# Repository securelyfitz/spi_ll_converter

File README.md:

# spi_ll_converter
Sparkfun's logic level converter modified to add SPI headers

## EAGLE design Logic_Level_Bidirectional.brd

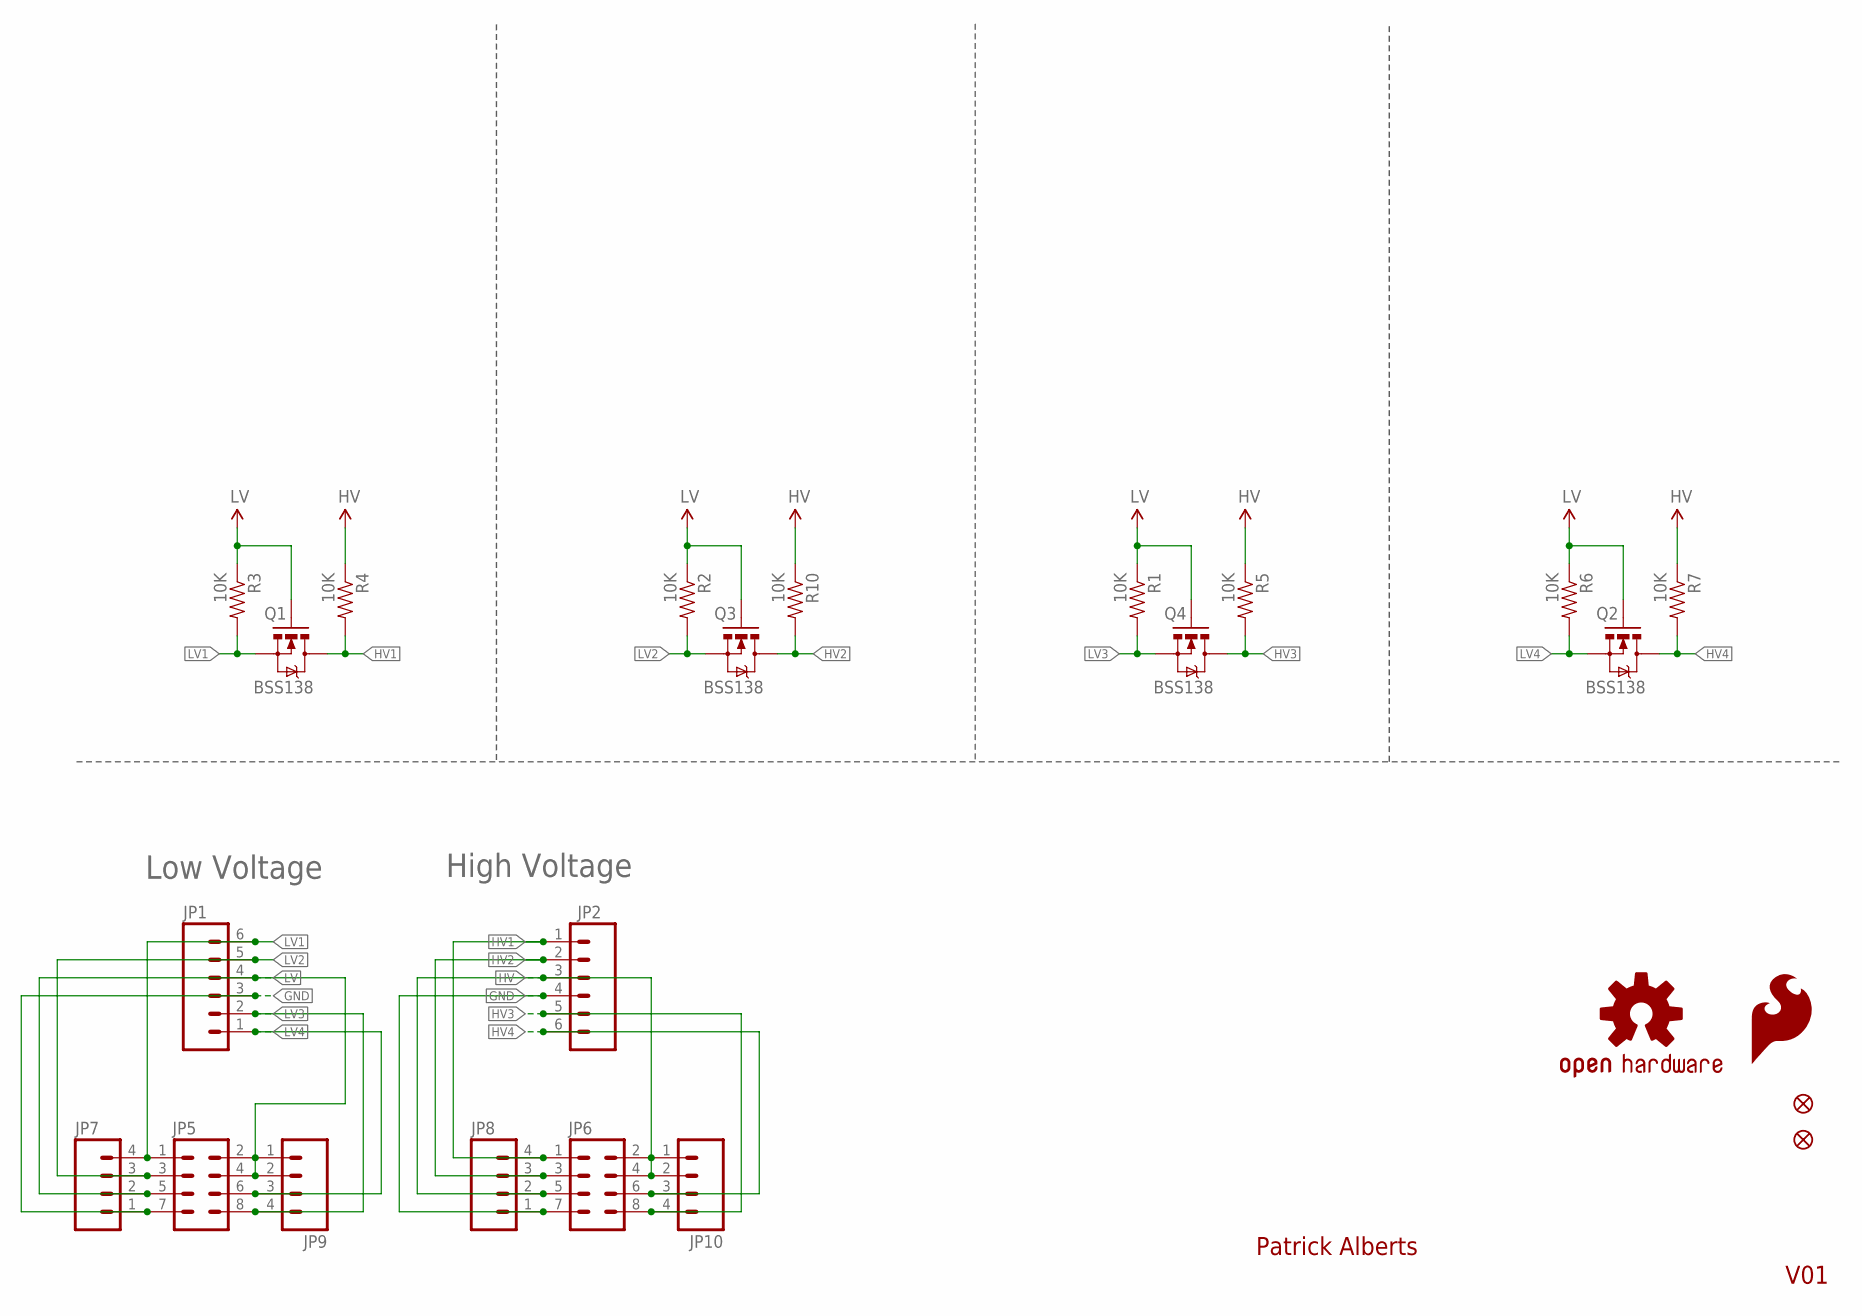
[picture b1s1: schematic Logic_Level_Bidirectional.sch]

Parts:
JP1, JP2: M06SIP; 1X06
JP3, JP4: FIDUCIALUFIDUCIAL; MICRO-FIDUCIAL
JP5, JP6: M04X2; 2X4
JP7, JP8: M04LOCK; 1X04_LOCK
JP9, JP10: M04PTH; 1X04
LOGO1: SFE_LOGO_FLAME.1_INCH; SFE_LOGO_FLAME_.1
LOGO2: OSHW-LOGOS; OSHW-LOGO-S
Q1, Q2, Q3, Q4: BSS138; SOT23-3
R1, R2, R3, R4, R5, R6, R7, R10: 10K; 0603-RES

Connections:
GND: JP1.3, JP2.4, JP5.7, JP6.7, JP7.1, JP8.1
HV: JP2.3, JP6.2, JP6.4, JP6.5, JP8.2, JP10.1, JP10.2, R4.1, R5.1, R7.1, R10.1
HV1: JP2.1, JP6.1, JP8.4, Q1.3 (D), R4.2
HV2: JP2.2, JP6.3, JP8.3, Q3.3 (D), R10.2
HV3: JP2.5, JP6.8, JP10.4, Q4.3 (D), R5.2
HV4: JP2.6, JP6.6, JP10.3, Q2.3 (D), R7.2
LV: JP1.4, JP5.2, JP5.4, JP5.5, JP7.2, JP9.1, JP9.2, Q1.1 (G), Q2.1 (G), Q3.1 (G), Q4.1 (G), R1.1, R2.1, R3.1, R6.1
LV1: JP1.6, JP5.1, JP7.4, Q1.2 (S), R3.2
LV2: JP1.5, JP5.3, JP7.3, Q3.2 (S), R2.2
LV3: JP1.2, JP5.8, JP9.4, Q4.2 (S), R1.2
LV4: JP1.1, JP5.6, JP9.3, Q2.2 (S), R6.2

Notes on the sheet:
High Voltage
Low Voltage
V01
Patrick Alberts

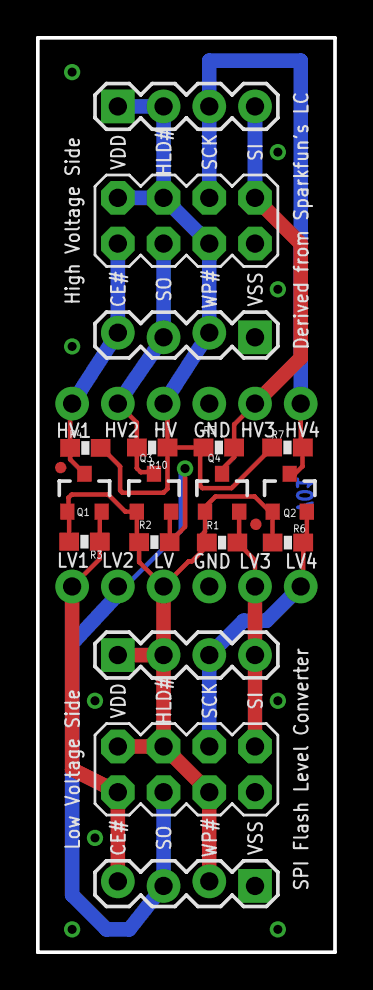
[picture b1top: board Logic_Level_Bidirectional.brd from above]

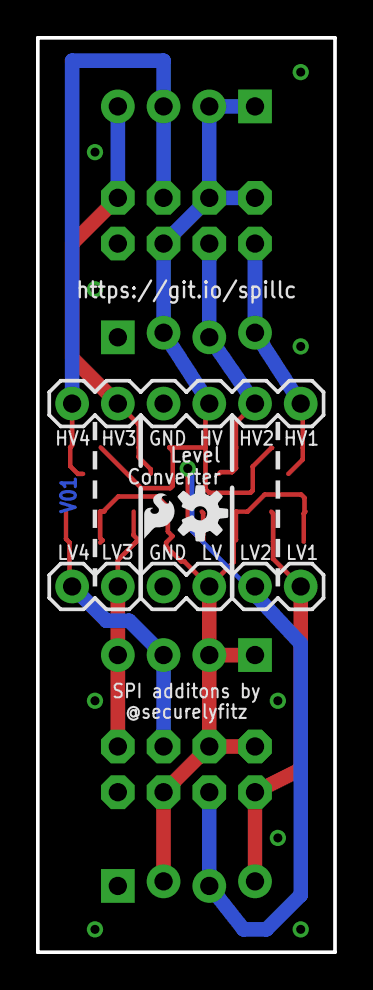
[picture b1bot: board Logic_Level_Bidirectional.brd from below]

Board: 2 copper layers, 16.5 x 50.8 mm, 24 parts (4 on the bottom side), 11 nets.

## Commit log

2015-07-06 initial version. started from sparkfun's level shifter, added headers for spi clips and programmer in both directions
2015-07-06 adding board images

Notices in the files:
parts and their libraries:
SparkFun-Aesthetics: Licensing: CC v3.0 Share-Alike You are welcome to use this library for commercial purposes.
SparkFun-Connectors: Licensing: Creative Commons ShareAlike 4.0 International - https://creativecommons.org/licenses/by-sa/4.0
SparkFun-Aesthetics: Released under the Creative Commons
